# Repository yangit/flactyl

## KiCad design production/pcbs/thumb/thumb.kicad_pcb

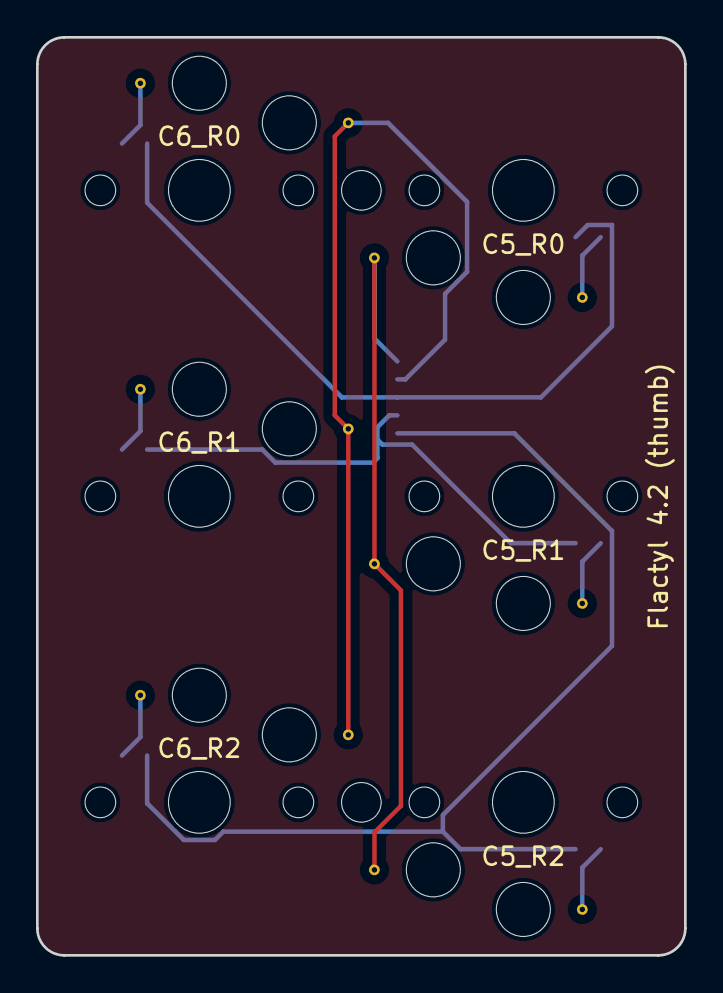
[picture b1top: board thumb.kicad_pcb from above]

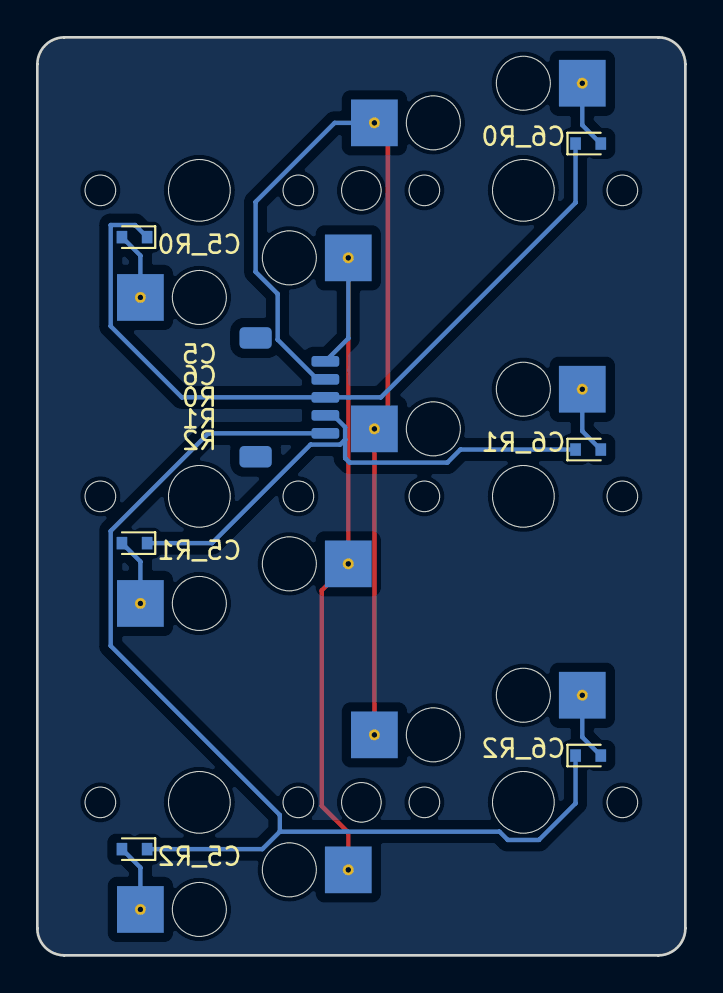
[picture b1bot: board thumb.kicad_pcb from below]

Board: 2 copper layers, 36.0 x 51.0 mm, 18 parts (13 on the bottom side), 11 nets.

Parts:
D1, D2, D3, D4, D5, D6: D_SOD-523
H1, H2: MountingHole_2.2mm_M2
JC1: JST_SH_SM05B-SRSS-TB_1x05-1MP_P1.00mm_Horizontal
S1, S2, S3, S4, S5, S6: Kailh_socket_PG1350_no_silk
T1: Flactyl 4.2 (thumb); somelogo
T2: x; somelogo
T3: y; somelogo

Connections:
C5: JC1.1, S1.2, S1.4, S2.2, S2.4, S3.2, S3.4
C5_R0D: D1.2, S1.1, S1.3
C5_R1D: D2.2, S2.1, S2.3
C5_R2D: D3.2, S3.1, S3.3
C6: JC1.2, S4.2, S4.4, S5.2, S5.4, S6.2, S6.4
C6_R0D: D4.2, S4.1, S4.3
C6_R1D: D5.2, S5.1, S5.3
C6_R2D: D6.2, S6.1, S6.3
R0: D1.1, D4.1, JC1.3
R1: D2.1, D5.1, JC1.4
R2: D3.1, D6.1, JC1.5
